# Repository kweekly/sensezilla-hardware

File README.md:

sensezilla-hardware
===================

SinBerBEST Sensing Project [hardware projects]

Contains EAGLE files for the circuit boards we are building for power_monitoring, radio boards, etc..

Do not commit EAGLE's massive ammount of "undo" files (should be handled by .gitignore)

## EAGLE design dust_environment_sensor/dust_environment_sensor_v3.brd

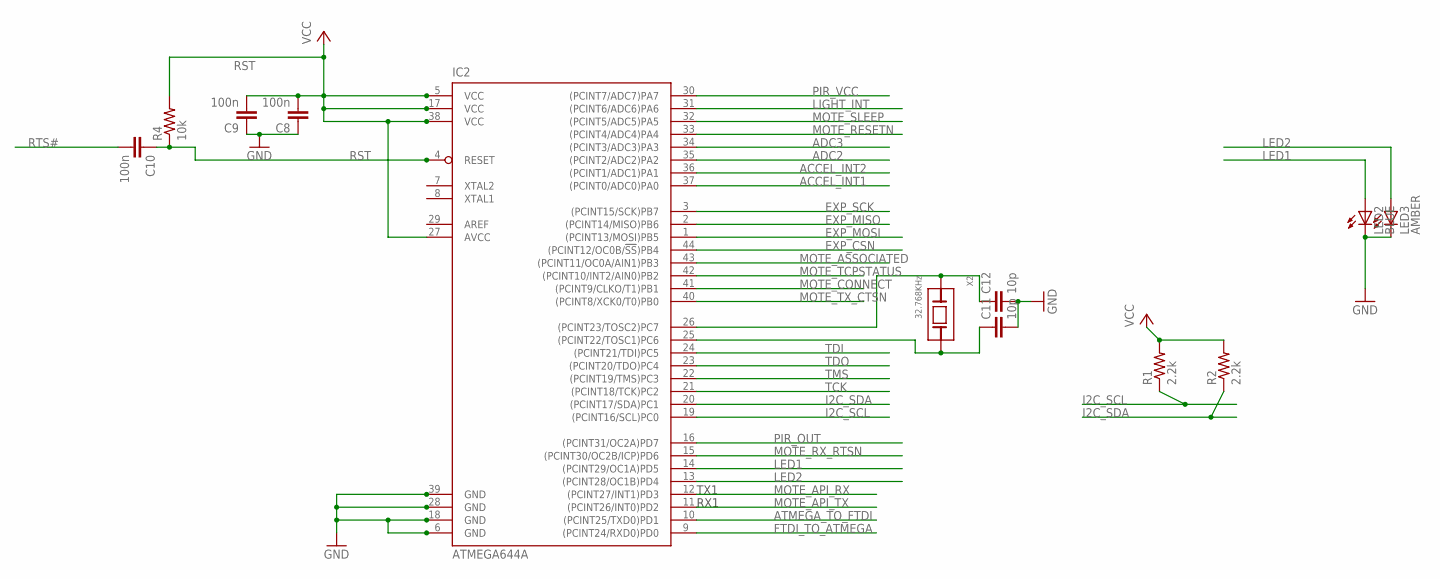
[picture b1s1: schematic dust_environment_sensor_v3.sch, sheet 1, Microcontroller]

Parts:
C8, C9, C10: 100n; C0603
C11, C12: 10p; C0603
IC2: ATMEGA644A; TQFP44
LED2: BLUE; CHIPLED_0805
LED3: AMBER; CHIPLED_0805
R1, R2: 2.2k; R0603
R4: 10k; R0603
X2: 32.768KHz; ABS07

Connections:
ACCEL_INT1: IC2.37 ((PCINT0/ADC0)PA0); also elsewhere on the board
ACCEL_INT2: IC2.36 ((PCINT1/ADC1)PA1); also elsewhere on the board
ADC2: IC2.35 ((PCINT2/ADC2)PA2); also elsewhere on the board
ADC3: IC2.34 ((PCINT3/ADC3)PA3); also elsewhere on the board
ATMEGA_TO_FTDI: IC2.10 ((PCINT25/TXD0)PD1); also elsewhere on the board
EXP_CSN: IC2.44 ((PCINT12/OC0B/!SS!)PB4); also elsewhere on the board
EXP_MISO: IC2.2 ((PCINT14/MISO)PB6); also elsewhere on the board
EXP_MOSI: IC2.1 ((PCINT13/MOSI)PB5); also elsewhere on the board
EXP_SCK: IC2.3 ((PCINT15/SCK)PB7); also elsewhere on the board
FTDI_TO_ATMEGA: IC2.9 ((PCINT24/RXD0)PD0); also elsewhere on the board
GND: C8.1, C9.1, C11.2, C12.2, IC2.6 (GND), IC2.18 (GND), IC2.28 (GND), IC2.39 (GND), LED2.C, LED3.C; also elsewhere on the board
I2C_SCL: IC2.19 ((PCINT16/SCL)PC0), R1.1; also elsewhere on the board
I2C_SDA: IC2.20 ((PCINT17/SDA)PC1), R2.1; also elsewhere on the board
LED1: IC2.14 ((PCINT29/OC1A)PD5), LED2.A
LED2: IC2.13 ((PCINT28/OC1B)PD4), LED3.A
LIGHT_INT: IC2.31 ((PCINT6/ADC6)PA6); also elsewhere on the board
MOTE_API_RX: IC2.12 ((PCINT27/INT1)PD3); also elsewhere on the board
MOTE_API_TX: IC2.11 ((PCINT26/INT0)PD2); also elsewhere on the board
MOTE_ASSOCIATED: IC2.43 ((PCINT11/OC0A/AIN1)PB3); also elsewhere on the board
MOTE_CONNECT: IC2.41 ((PCINT9/CLKO/T1)PB1); also elsewhere on the board
MOTE_RESETN: IC2.33 ((PCINT4/ADC4)PA4); also elsewhere on the board
MOTE_RX_RTSN: IC2.15 ((PCINT30/OC2B/ICP)PD6); also elsewhere on the board
MOTE_SLEEP: IC2.32 ((PCINT5/ADC5)PA5); also elsewhere on the board
MOTE_TCPSTATUS: IC2.42 ((PCINT10/INT2/AIN0)PB2); also elsewhere on the board
MOTE_TX_CTSN: IC2.40 ((PCINT8/XCK0/T0)PB0); also elsewhere on the board
unnamed: C11.1, IC2.25 ((PCINT22/TOSC1)PC6), X2.2 (B)
unnamed: C12.1, IC2.26 ((PCINT23/TOSC2)PC7), X2.1 (A)
PIR_OUT: IC2.16 ((PCINT31/OC2A)PD7); also elsewhere on the board
PIR_VCC: IC2.30 ((PCINT7/ADC7)PA7); also elsewhere on the board
RST: C10.1, IC2.4 (RESET), R4.1; also elsewhere on the board
RTS#: C10.2; also elsewhere on the board
TCK: IC2.21 ((PCINT18/TCK)PC2); also elsewhere on the board
TDI: IC2.24 ((PCINT21/TDI)PC5); also elsewhere on the board
TDO: IC2.23 ((PCINT20/TDO)PC4); also elsewhere on the board
TMS: IC2.22 ((PCINT19/TMS)PC3); also elsewhere on the board
VCC: C8.2, C9.2, IC2.5 (VCC), IC2.17 (VCC), IC2.27 (AVCC), IC2.38 (VCC), R1.2, R2.2, R4.2; also elsewhere on the board

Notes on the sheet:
TX1
RX1

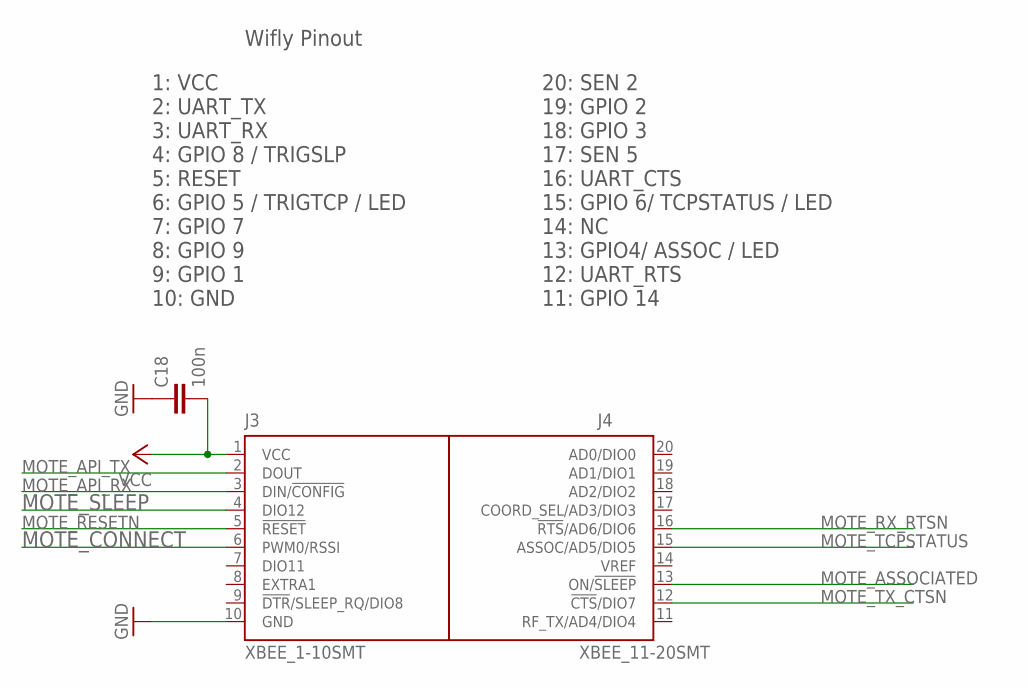
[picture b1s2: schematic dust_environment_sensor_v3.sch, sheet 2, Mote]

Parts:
C18: 100n; C0603
J3: XBEE_1-10SMT; XBEE_1-10_SMT
J4: XBEE_11-20SMT; XBEE_11-20_SMT

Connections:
GND: C18.1, J3.10 (GND); also elsewhere on the board
MOTE_API_RX: J3.3 (DIN/!CONFIG); also elsewhere on the board
MOTE_API_TX: J3.2 (DOUT); also elsewhere on the board
MOTE_ASSOCIATED: J4.13 (ON/!SLEEP); also elsewhere on the board
MOTE_CONNECT: J3.6 (PWM0/RSSI); also elsewhere on the board
MOTE_RESETN: J3.5 (!RESET); also elsewhere on the board
MOTE_RX_RTSN: J4.16 (!RTS!/AD6/DIO6); also elsewhere on the board
MOTE_SLEEP: J3.4 (DIO12); also elsewhere on the board
MOTE_TCPSTATUS: J4.15 (ASSOC/AD5/DIO5); also elsewhere on the board
MOTE_TX_CTSN: J4.12 (!CTS!/DIO7); also elsewhere on the board
VCC: C18.2, J3.1 (VCC); also elsewhere on the board

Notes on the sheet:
Wifly Pinout
1: VCC 2: UART_TX 3: UART_RX 4: GPIO 8 / TRIGSLP 5: RESET 6: GPIO 5 / TRIGTCP / LED 7: GPIO 7 8: GPIO 9 9: GPIO 1 10: GND
20: SEN 2 19: GPIO 2 18: GPIO 3 17: SEN 5 16: UART_CTS 15: GPIO 6/ TCPSTATUS / LED 14: NC 13: GPIO4/ ASSOC / LED 12: UART_RTS 11: GPIO 14

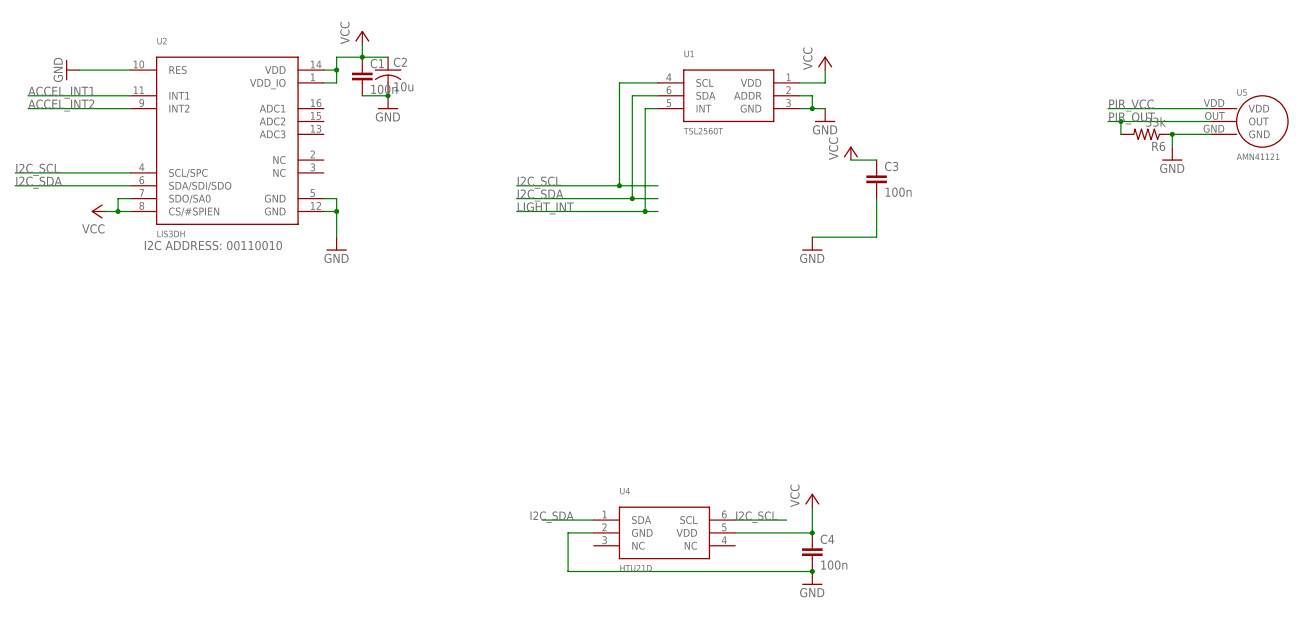
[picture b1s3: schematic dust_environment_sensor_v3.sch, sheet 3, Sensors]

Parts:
C1, C3, C4: 100n; C0603
C2: 10u; C0603
R6: 33k; R0603
U1: TSL2560T; T_TAOS
U2: LIS3DH; LGA16_ST
U4: HTU21D
U5: AMN41121

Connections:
ACCEL_INT1: U2.11 (INT1); also elsewhere on the board
ACCEL_INT2: U2.9 (INT2); also elsewhere on the board
GND: C1.2, C2.2, C3.2, C4.2, R6.1, U1.2 (ADDR), U1.3 (GND), U2.5 (GND), U2.10 (RES), U2.12 (GND), U4.2 (GND), U5.GND; also elsewhere on the board
I2C_SCL: U1.4 (SCL), U2.4 (SCL/SPC), U4.6 (SCL); also elsewhere on the board
I2C_SDA: U1.6 (SDA), U2.6 (SDA/SDI/SDO), U4.1 (SDA); also elsewhere on the board
LIGHT_INT: U1.5 (INT); also elsewhere on the board
PIR_OUT: R6.2, U5.OUT; also elsewhere on the board
PIR_VCC: U5.VDD; also elsewhere on the board
VCC: C1.1, C2.1, C3.1, C4.1, U1.1 (VDD), U2.1 (VDD_IO), U2.7 (SDO/SA0), U2.8 (CS/#SPIEN), U2.14 (VDD), U4.5 (VDD); also elsewhere on the board

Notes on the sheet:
I2C ADDRESS: 00110010

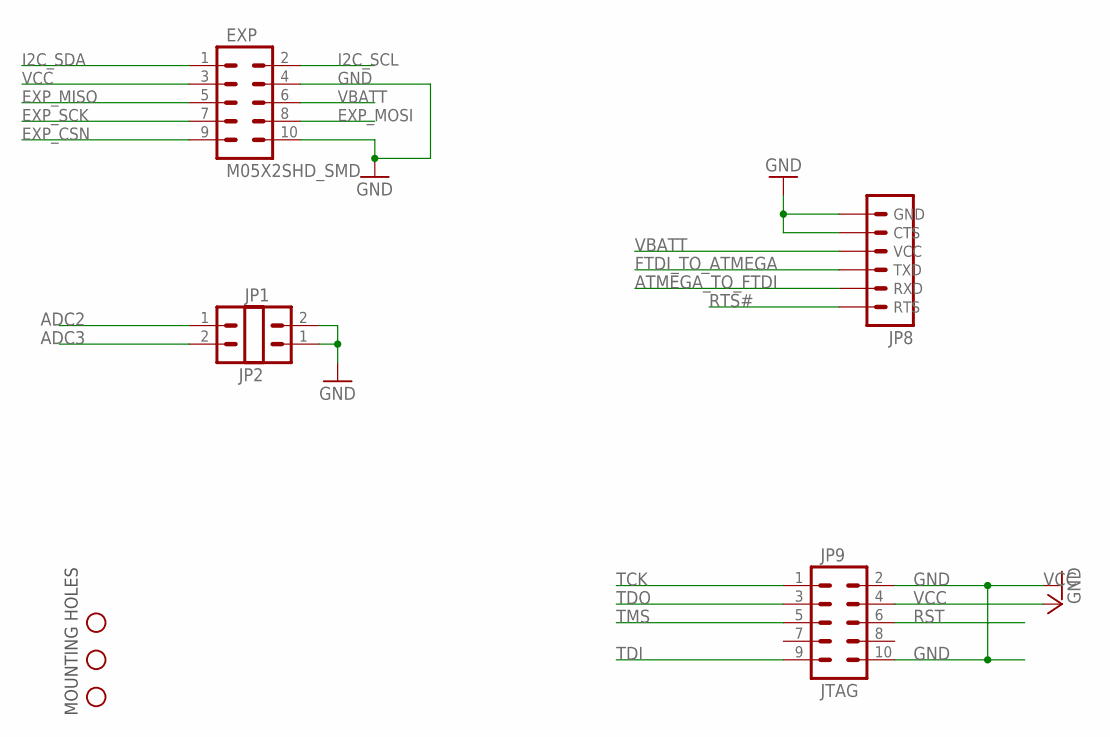
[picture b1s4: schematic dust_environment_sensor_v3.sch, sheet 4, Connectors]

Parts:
EXP: M05X2SHD_SMD; 2X5-SHROUDED_SMD
JP1, JP2: M02PTH; 1X02
JP8: FTDI_CABLESIP; 1X06
JP9: JTAG; 2X5-SHROUDED_SMD
STANDOFF1, STANDOFF2, STANDOFF3: STAND-OFF

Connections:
ADC2: JP2.1; also elsewhere on the board
ADC3: JP2.2; also elsewhere on the board
ATMEGA_TO_FTDI: JP8.5 (RXD); also elsewhere on the board
EXP_CSN: EXP.9; also elsewhere on the board
EXP_MISO: EXP.5; also elsewhere on the board
EXP_MOSI: EXP.8; also elsewhere on the board
EXP_SCK: EXP.7; also elsewhere on the board
FTDI_TO_ATMEGA: JP8.4 (TXD); also elsewhere on the board
GND: EXP.4, EXP.10, JP1.1, JP1.2, JP8.1 (GND), JP8.2 (CTS), JP9.2, JP9.10; also elsewhere on the board
I2C_SCL: EXP.2; also elsewhere on the board
I2C_SDA: EXP.1; also elsewhere on the board
RST: JP9.6; also elsewhere on the board
RTS#: JP8.6 (RTS); also elsewhere on the board
TCK: JP9.1; also elsewhere on the board
TDI: JP9.9; also elsewhere on the board
TDO: JP9.3; also elsewhere on the board
TMS: JP9.5; also elsewhere on the board
VBATT: EXP.6, JP8.3 (VCC); also elsewhere on the board
VCC: EXP.3, JP9.4; also elsewhere on the board

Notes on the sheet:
MOUNTING HOLES

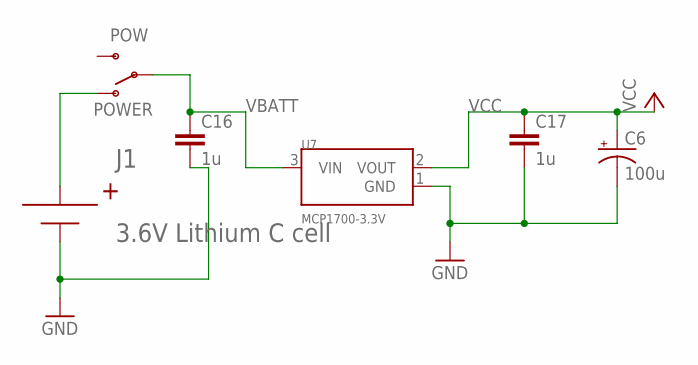
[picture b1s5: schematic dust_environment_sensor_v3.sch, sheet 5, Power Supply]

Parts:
C6: 100u; EIA7343
C16, C17: 1u; C0603
J1: 3.6V Lithium C cell; BX0036_NOHOLES
POW: POWER; JS102011SAQN
U7: MCP1700-3.3V; SOT23-3

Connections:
GND: C6.C (-), C16.2, C17.2, J1.NEG, U7.1 (GND); also elsewhere on the board
unnamed: J1.POS, POW.1 (O)
VBATT: C16.1, POW.C, U7.3 (VIN); also elsewhere on the board
VCC: C6.A (+), C17.1, U7.2 (VOUT); also elsewhere on the board

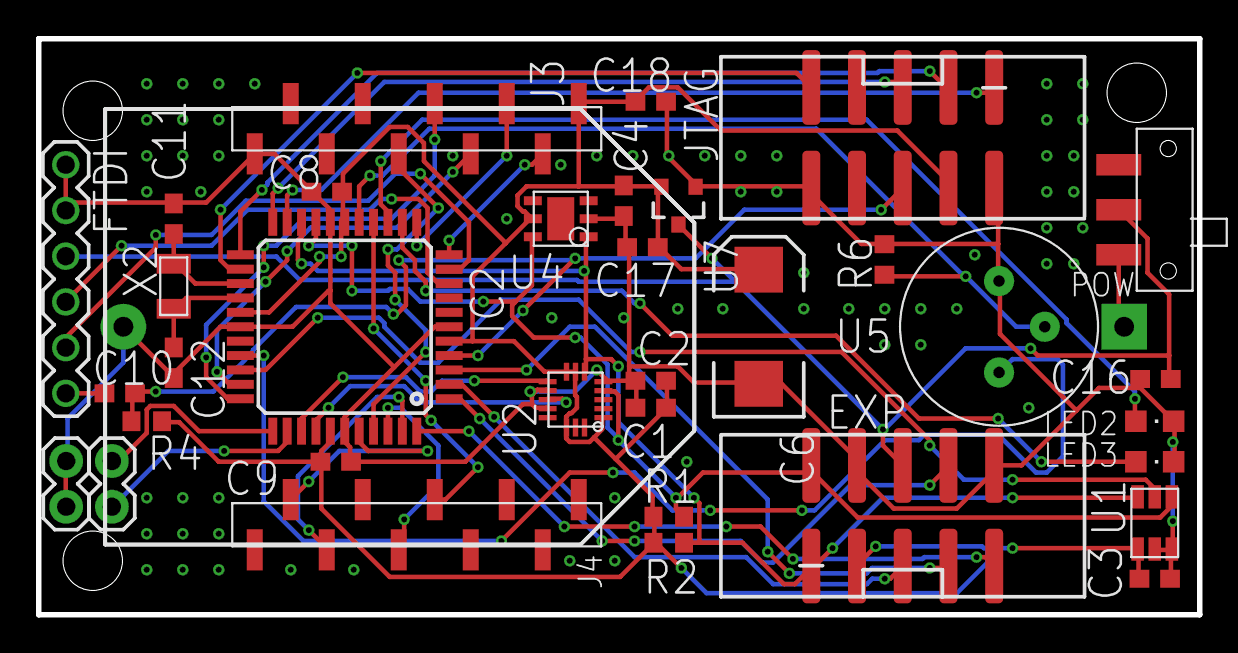
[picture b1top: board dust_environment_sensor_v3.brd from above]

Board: 2 copper layers, 64.5 x 32.0 mm, 38 parts (1 on the bottom side), 38 nets.

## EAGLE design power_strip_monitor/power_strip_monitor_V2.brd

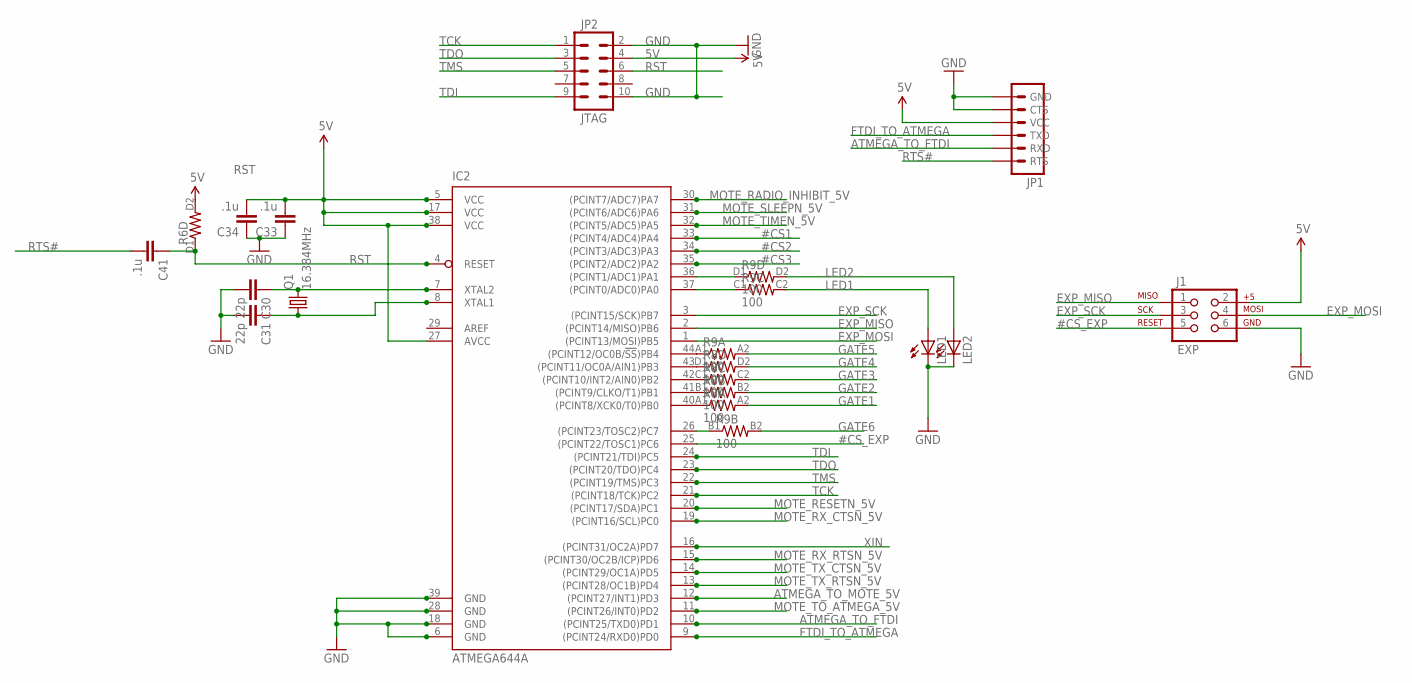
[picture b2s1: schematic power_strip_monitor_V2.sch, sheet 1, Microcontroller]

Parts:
C30, C31: 22p; 0603
C33, C34, C41: .1u; 0603
IC2: ATMEGA644A; TQFP44
J1: EXP; 2X3
JP1: FTDI_CABLESIP; 1X06
JP2: JTAG; AVR_ICSP
LED1, LED2: LEDCHIPLED_0805; CHIPLED_0805
Q1: 16.384MHz; HC49UP
R6: RESISTOR-ARRAY; 1206_NETWORK
R8, R9: 100; 1206_NETWORK

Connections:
5V: C33.2, C34.2, IC2.5 (VCC), IC2.17 (VCC), IC2.27 (AVCC), IC2.38 (VCC), J1.2, JP1.3 (VCC), JP2.4, R6.D2 (2); also elsewhere on the board
#CS1: IC2.33 ((PCINT4/ADC4)PA4); also elsewhere on the board
#CS2: IC2.34 ((PCINT3/ADC3)PA3); also elsewhere on the board
#CS3: IC2.35 ((PCINT2/ADC2)PA2); also elsewhere on the board
#CS_EXP: IC2.25 ((PCINT22/TOSC1)PC6), J1.5
ATMEGA_TO_FTDI: IC2.10 ((PCINT25/TXD0)PD1), JP1.5 (RXD)
ATMEGA_TO_MOTE_5V: IC2.12 ((PCINT27/INT1)PD3); also elsewhere on the board
EXP_MISO: IC2.2 ((PCINT14/MISO)PB6), J1.1
EXP_MOSI: IC2.1 ((PCINT13/MOSI)PB5), J1.4
EXP_SCK: IC2.3 ((PCINT15/SCK)PB7), J1.3
FTDI_TO_ATMEGA: IC2.9 ((PCINT24/RXD0)PD0), JP1.4 (TXD)
GATE1: R8.A2 (2); also elsewhere on the board
GATE2: R8.B2 (2); also elsewhere on the board
GATE3: R8.C2 (2); also elsewhere on the board
GATE4: R8.D2 (2); also elsewhere on the board
GATE5: R9.A2 (2); also elsewhere on the board
GATE6: R9.B2 (2); also elsewhere on the board
GND: C30.2, C31.2, C33.1, C34.1, IC2.6 (GND), IC2.18 (GND), IC2.28 (GND), IC2.39 (GND), J1.6, JP1.1 (GND), JP1.2 (CTS), JP2.2, JP2.10, LED1.C, LED2.C; also elsewhere on the board
LED1: LED1.A, R9.C2 (2)
LED2: LED2.A, R9.D2 (2)
MOTE_RADIO_INHIBIT_5V: IC2.30 ((PCINT7/ADC7)PA7); also elsewhere on the board
MOTE_RESETN_5V: IC2.20 ((PCINT17/SDA)PC1); also elsewhere on the board
MOTE_RX_CTSN_5V: IC2.19 ((PCINT16/SCL)PC0); also elsewhere on the board
MOTE_RX_RTSN_5V: IC2.15 ((PCINT30/OC2B/ICP)PD6); also elsewhere on the board
MOTE_SLEEPN_5V: IC2.31 ((PCINT6/ADC6)PA6); also elsewhere on the board
MOTE_TIMEN_5V: IC2.32 ((PCINT5/ADC5)PA5); also elsewhere on the board
MOTE_TO_ATMEGA_5V: IC2.11 ((PCINT26/INT0)PD2); also elsewhere on the board
MOTE_TX_CTSN_5V: IC2.14 ((PCINT29/OC1A)PD5); also elsewhere on the board
MOTE_TX_RTSN_5V: IC2.13 ((PCINT28/OC1B)PD4); also elsewhere on the board
unnamed: C30.1, IC2.7 (XTAL2), Q1.2
unnamed: C31.1, IC2.8 (XTAL1), Q1.1
unnamed: IC2.40 ((PCINT8/XCK0/T0)PB0), R8.A1 (1)
unnamed: IC2.41 ((PCINT9/CLKO/T1)PB1), R8.B1 (1)
unnamed: IC2.42 ((PCINT10/INT2/AIN0)PB2), R8.C1 (1)
unnamed: IC2.43 ((PCINT11/OC0A/AIN1)PB3), R8.D1 (1)
unnamed: IC2.44 ((PCINT12/OC0B/!SS!)PB4), R9.A1 (1)
unnamed: IC2.26 ((PCINT23/TOSC2)PC7), R9.B1 (1)
unnamed: IC2.36 ((PCINT1/ADC1)PA1), R9.D1 (1)
unnamed: IC2.37 ((PCINT0/ADC0)PA0), R9.C1 (1)
RST: C41.1, IC2.4 (RESET), JP2.6, R6.D1 (1)
RTS#: C41.2, JP1.6 (RTS)
TCK: IC2.21 ((PCINT18/TCK)PC2), JP2.1
TDI: IC2.24 ((PCINT21/TDI)PC5), JP2.9
TDO: IC2.23 ((PCINT20/TDO)PC4), JP2.3
TMS: IC2.22 ((PCINT19/TMS)PC3), JP2.5
XIN: IC2.16 ((PCINT31/OC2A)PD7); also elsewhere on the board

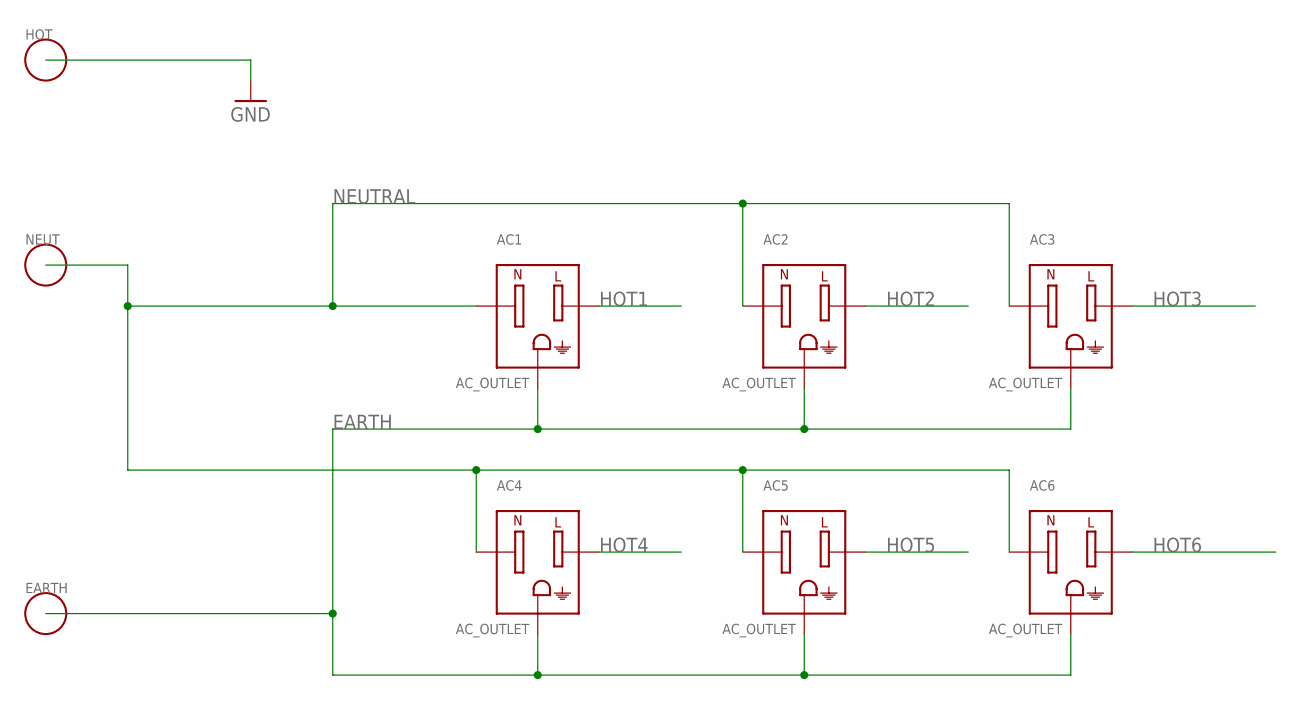
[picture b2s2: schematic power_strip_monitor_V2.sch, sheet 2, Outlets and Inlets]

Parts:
AC1, AC2, AC3, AC4, AC5, AC6: AC_OUTLET; 3-213598-2
EARTH: 1P_HOLE; 14GAUGE_HOLE
HOT: 1P_HOLE; 14GAUGE_HOLE
NEUT: 1P_HOLE; 14GAUGE_HOLE

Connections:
EARTH: AC1.3 (EARTH), AC2.3 (EARTH), AC3.3 (EARTH), AC4.3 (EARTH), AC5.3 (EARTH), AC6.3 (EARTH), EARTH.P$1
GND: HOT.P$1; also elsewhere on the board
HOT1: AC1.2 (L); also elsewhere on the board
HOT2: AC2.2 (L); also elsewhere on the board
HOT3: AC3.2 (L); also elsewhere on the board
HOT4: AC4.2 (L); also elsewhere on the board
HOT5: AC5.2 (L); also elsewhere on the board
HOT6: AC6.2 (L); also elsewhere on the board
NEUTRAL: AC1.1 (N), AC2.1 (N), AC3.1 (N), AC4.1 (N), AC5.1 (N), AC6.1 (N), NEUT.P$1; also elsewhere on the board

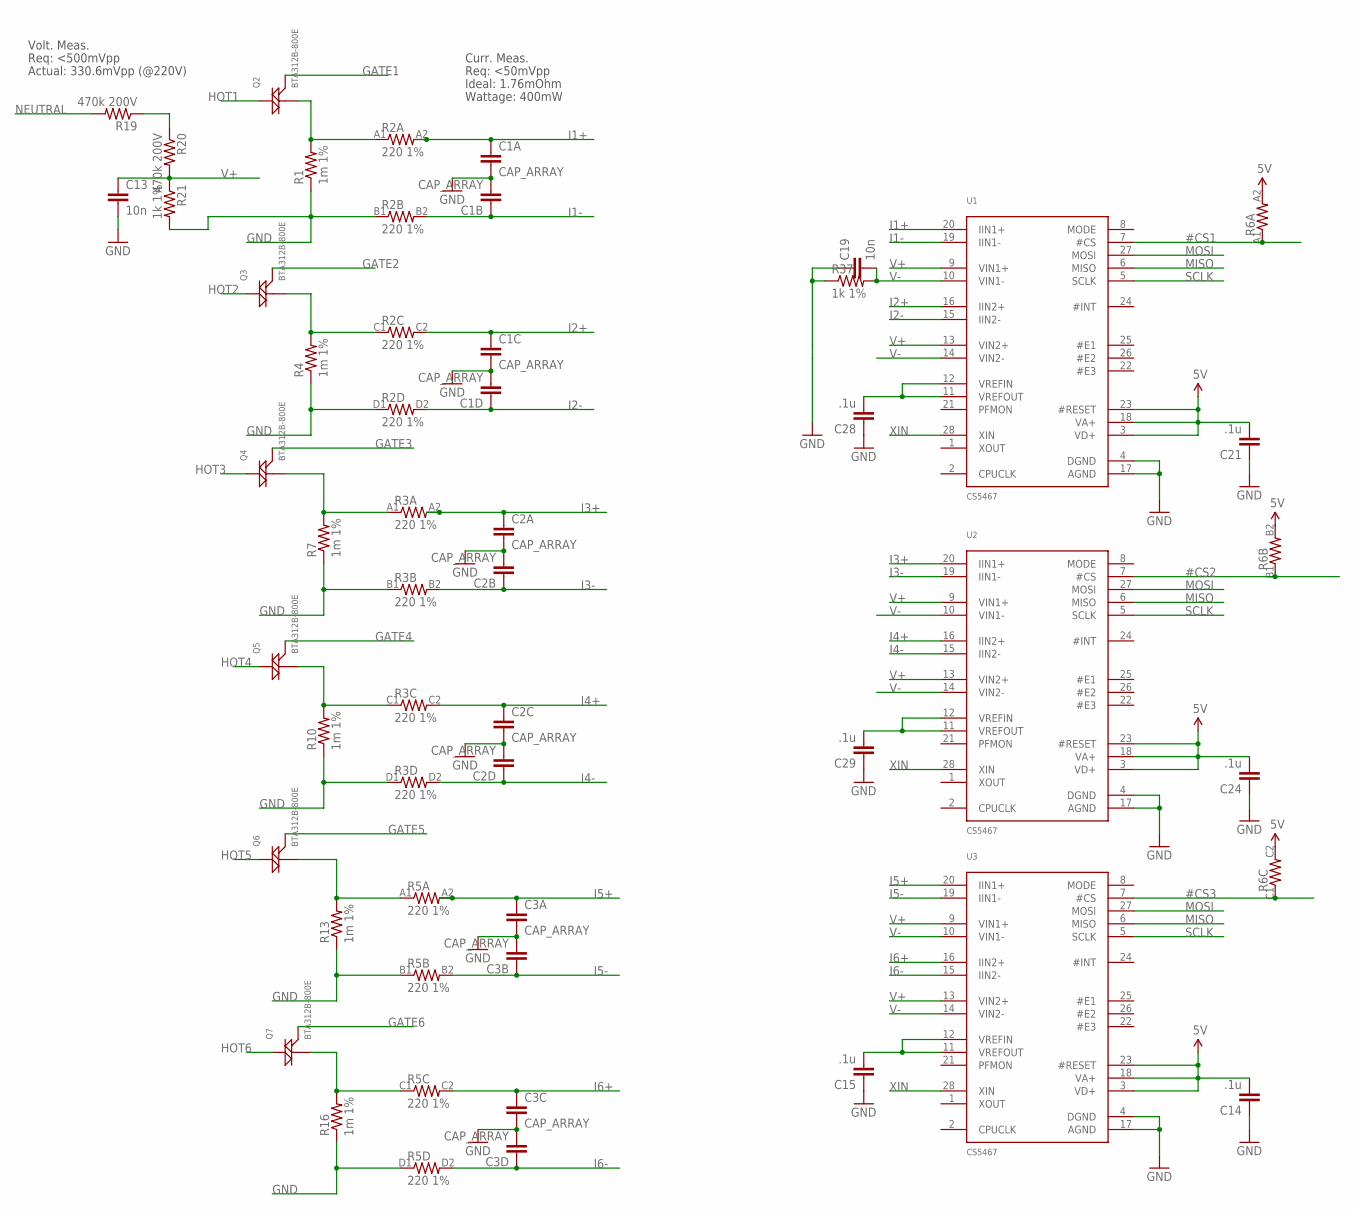
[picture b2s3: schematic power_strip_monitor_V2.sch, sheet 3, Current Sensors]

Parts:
C1, C2, C3: CAP_ARRAY; 1206_NETWORK
C13, C19: 10n; 0603
C14, C15, C21, C24, C28, C29: .1u; 0603
Q2, Q3, Q4, Q5, Q6, Q7: BTA312B-800E; D2PACK_NXP
R1, R4, R7, R10, R13, R16: 1m 1%; R2512
R2, R3, R5: 220 1%; 1206_NETWORK
R6: RESISTOR-ARRAY; 1206_NETWORK
R19, R20: 470k 200V; 1206
R21, R37: 1k 1%; 0603
U1, U2, U3: CS5467; SSOP28L_CIRRUS

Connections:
5V: C14.2, C21.2, C24.2, R6.A2 (2), R6.B2 (2), R6.C2 (2), U1.3 (VD+), U1.18 (VA+), U1.23 (#RESET), U2.3 (VD+), U2.18 (VA+), U2.23 (#RESET), U3.3 (VD+), U3.18 (VA+), U3.23 (#RESET); also elsewhere on the board
#CS1: R6.A1 (1), U1.7 (#CS); also elsewhere on the board
#CS2: R6.B1 (1), U2.7 (#CS); also elsewhere on the board
#CS3: R6.C1 (1), U3.7 (#CS); also elsewhere on the board
GATE1: Q2.3 (G); also elsewhere on the board
GATE2: Q3.3 (G); also elsewhere on the board
GATE3: Q4.3 (G); also elsewhere on the board
GATE4: Q5.3 (G); also elsewhere on the board
GATE5: Q6.3 (G); also elsewhere on the board
GATE6: Q7.3 (G); also elsewhere on the board
GND: C1.A2 (2), C1.B2 (2), C1.C2 (2), C1.D2 (2), C2.A2 (2), C2.B2 (2), C2.C2 (2), C2.D2 (2), C3.A2 (2), C3.B2 (2), C3.C2 (2), C3.D2 (2), C13.2, C14.1, C15.1, C19.1, C21.1, C24.1, C28.1, C29.1, R1.1, R2.B1 (1), R2.D1 (1), R3.B1 (1), R3.D1 (1), R4.1, R5.B1 (1), R5.D1 (1), R7.1, R10.1, R13.1, R16.1, R21.2, R37.1, U1.4 (DGND), U1.17 (AGND), U2.4 (DGND), U2.17 (AGND), U3.4 (DGND), U3.17 (AGND); also elsewhere on the board
HOT1: Q2.2 (M2); also elsewhere on the board
HOT2: Q3.2 (M2); also elsewhere on the board
HOT3: Q4.2 (M2); also elsewhere on the board
HOT4: Q5.2 (M2); also elsewhere on the board
HOT5: Q6.2 (M2); also elsewhere on the board
HOT6: Q7.2 (M2); also elsewhere on the board
HRET1: Q2.1 (M1), R1.2, R2.A1 (1)
HRET2: Q3.1 (M1), R2.C1 (1), R4.2
HRET3: Q4.1 (M1), R3.A1 (1), R7.2
HRET4: Q5.1 (M1), R3.C1 (1), R10.2
HRET5: Q6.1 (M1), R5.A1 (1), R13.2
HRET6: Q7.1 (M1), R5.C1 (1), R16.2
I1+: C1.A1 (1), R2.A2 (2), U1.20 (IIN1+)
I1-: C1.B1 (1), R2.B2 (2), U1.19 (IIN1-)
I2+: C1.C1 (1), R2.C2 (2), U1.16 (IIN2+)
I2-: C1.D1 (1), R2.D2 (2), U1.15 (IIN2-)
I3+: C2.A1 (1), R3.A2 (2), U2.20 (IIN1+)
I3-: C2.B1 (1), R3.B2 (2), U2.19 (IIN1-)
I4+: C2.C1 (1), R3.C2 (2), U2.16 (IIN2+)
I4-: C2.D1 (1), R3.D2 (2), U2.15 (IIN2-)
I5+: C3.A1 (1), R5.A2 (2), U3.20 (IIN1+)
I5-: C3.B1 (1), R5.B2 (2), U3.19 (IIN1-)
I6+: C3.C1 (1), R5.C2 (2), U3.16 (IIN2+)
I6-: C3.D1 (1), R5.D2 (2), U3.15 (IIN2-)
MISO: U1.6 (MISO), U2.6 (MISO), U3.6 (MISO)
MOSI: U1.27 (MOSI), U2.27 (MOSI), U3.27 (MOSI)
unnamed: R19.1, R20.1
unnamed: C15.2, U3.11 (VREFOUT), U3.12 (VREFIN)
unnamed: C29.2, U2.11 (VREFOUT), U2.12 (VREFIN)
unnamed: C28.2, U1.11 (VREFOUT), U1.12 (VREFIN)
NEUTRAL: R19.2; also elsewhere on the board
SCLK: U1.5 (SCLK), U2.5 (SCLK), U3.5 (SCLK)
V+: C13.1, R20.2, R21.1, U1.9 (VIN1+), U1.13 (VIN2+), U2.9 (VIN1+), U2.13 (VIN2+), U3.9 (VIN1+), U3.13 (VIN2+)
V-: C19.2, R37.2, U1.10 (VIN1-), U1.14 (VIN2-), U2.10 (VIN1-), U2.14 (VIN2-), U3.10 (VIN1-), U3.14 (VIN2-)
XIN: U1.28 (XIN), U2.28 (XIN), U3.28 (XIN); also elsewhere on the board

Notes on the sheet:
Req: <500mVpp
Actual: 330.6mVpp (@220V)
Volt. Meas.
Curr. Meas.
Req: <50mVpp
Ideal: 1.76mOhm
Wattage: 400mW

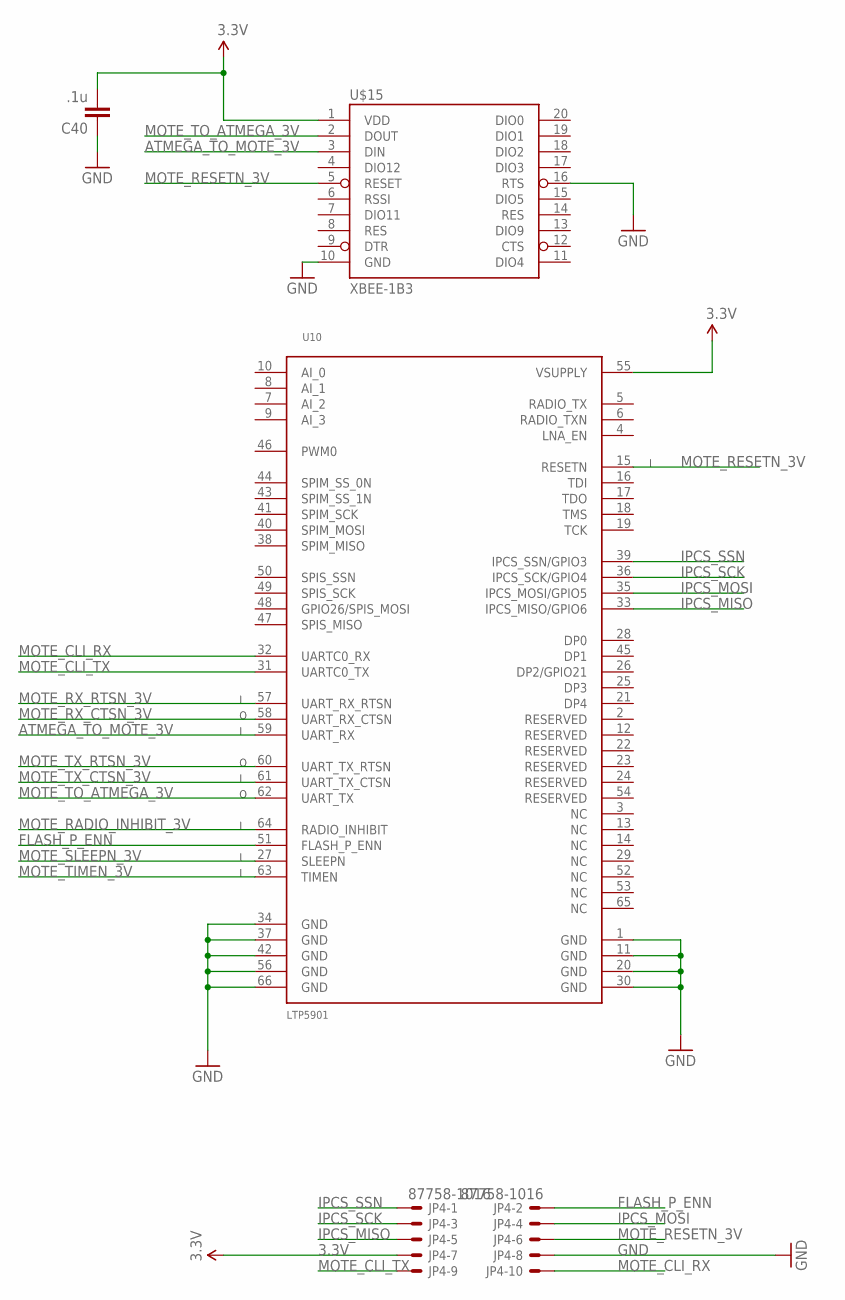
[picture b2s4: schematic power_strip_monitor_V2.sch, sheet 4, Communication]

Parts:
C40: .1u; 0603
JP4: 87758-1016
U10: LTP5901; LTP5901_MODULE
U$15: XBEE-1B3; XBEE-SMD

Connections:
3.3V: C40.2, JP4.7, U10.55 (VSUPPLY), U$15.1 (VDD); also elsewhere on the board
ATMEGA_TO_MOTE_3V: U10.59 (UART_RX), U$15.3 (DIN); also elsewhere on the board
FLASH_P_ENN: JP4.2, U10.51 (FLASH_P_ENN)
GND: C40.1, JP4.8, U10.1 (GND), U10.11 (GND), U10.20 (GND), U10.30 (GND), U10.34 (GND), U10.37 (GND), U10.42 (GND), U10.56 (GND), U10.66 (GND), U$15.10 (GND), U$15.16 (RTS); also elsewhere on the board
IPCS_MISO: JP4.5, U10.33 (IPCS_MISO/GPIO6)
IPCS_MOSI: JP4.4, U10.35 (IPCS_MOSI/GPIO5)
IPCS_SCK: JP4.3, U10.36 (IPCS_SCK/GPIO4)
IPCS_SSN: JP4.1, U10.39 (IPCS_SSN/GPIO3)
MOTE_CLI_RX: JP4.10, U10.32 (UARTC0_RX)
MOTE_CLI_TX: JP4.9, U10.31 (UARTC0_TX)
MOTE_RADIO_INHIBIT_3V: U10.64 (RADIO_INHIBIT); also elsewhere on the board
MOTE_RESETN_3V: JP4.6, U10.15 (RESETN), U$15.5 (RESET); also elsewhere on the board
MOTE_RX_CTSN_3V: U10.58 (UART_RX_CTSN); also elsewhere on the board
MOTE_RX_RTSN_3V: U10.57 (UART_RX_RTSN); also elsewhere on the board
MOTE_SLEEPN_3V: U10.27 (SLEEPN); also elsewhere on the board
MOTE_TIMEN_3V: U10.63 (TIMEN); also elsewhere on the board
MOTE_TO_ATMEGA_3V: U10.62 (UART_TX), U$15.2 (DOUT); also elsewhere on the board
MOTE_TX_CTSN_3V: U10.61 (UART_TX_CTSN); also elsewhere on the board
MOTE_TX_RTSN_3V: U10.60 (UART_TX_RTSN); also elsewhere on the board

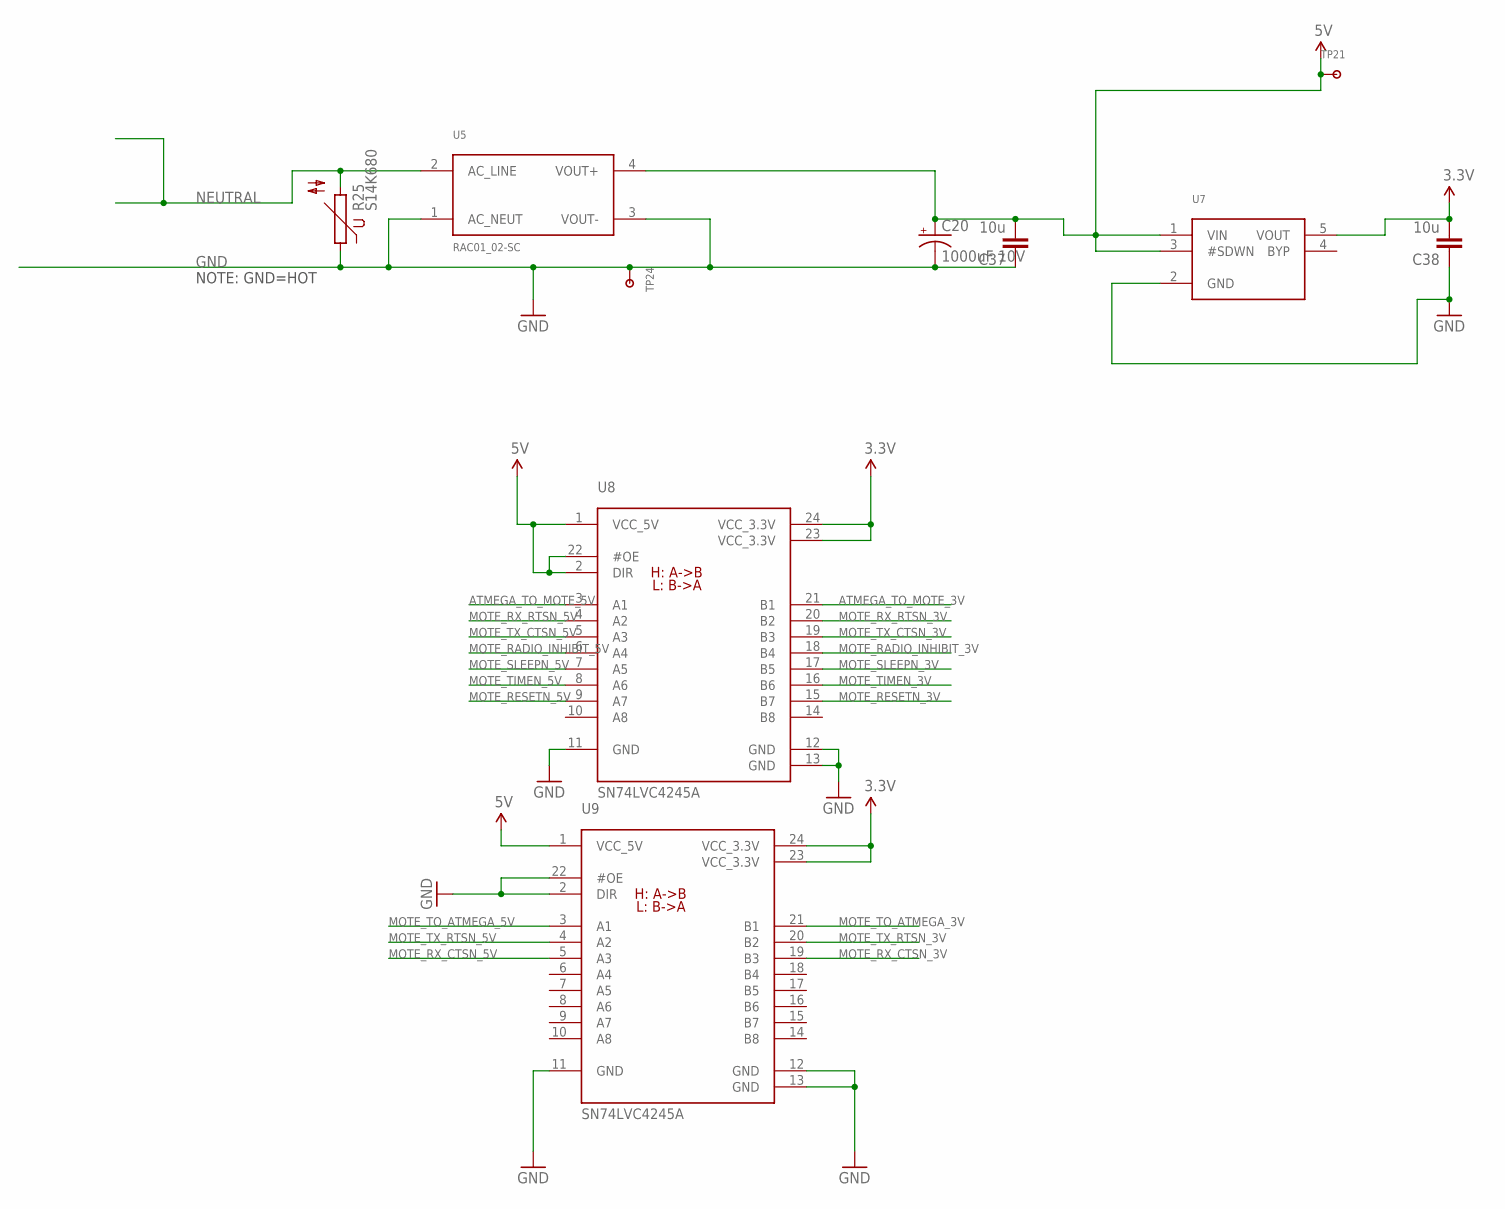
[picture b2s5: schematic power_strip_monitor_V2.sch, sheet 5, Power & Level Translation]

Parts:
C20: 1000uF 10V; CPOL-RADIAL-1000UF-63V
C37, C38: 10u; 0603
R25: S14K680
TP21, TP24: TESTPOINT100MIL; TESTPOINT-100MIL
U5: RAC01_02-SC
U7: LT1761-X; TSOT23-5_LINEAR
U8, U9: SN74LVC4245A; TSSOP24_TI

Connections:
3.3V: C38.2, U7.5 (VOUT), U8.23 (VCC_3.3V), U8.24 (VCC_3.3V), U9.23 (VCC_3.3V), U9.24 (VCC_3.3V); also elsewhere on the board
5V: C20.1 (+), C37.2, TP21.2, U5.4 (VOUT+), U7.1 (VIN), U7.3 (#SDWN), U8.1 (VCC_5V), U8.2 (DIR), U8.22 (#OE), U9.1 (VCC_5V); also elsewhere on the board
ATMEGA_TO_MOTE_3V: U8.21 (B1); also elsewhere on the board
ATMEGA_TO_MOTE_5V: U8.3 (A1); also elsewhere on the board
GND: C20.2 (-), C37.1, C38.1, R25.1, TP24.2, U5.1 (AC_NEUT), U5.3 (VOUT-), U7.2 (GND), U8.11 (GND), U8.12 (GND), U8.13 (GND), U9.2 (DIR), U9.11 (GND), U9.12 (GND), U9.13 (GND), U9.22 (#OE); also elsewhere on the board
MOTE_RADIO_INHIBIT_3V: U8.18 (B4); also elsewhere on the board
MOTE_RADIO_INHIBIT_5V: U8.6 (A4); also elsewhere on the board
MOTE_RESETN_3V: U8.15 (B7); also elsewhere on the board
MOTE_RESETN_5V: U8.9 (A7); also elsewhere on the board
MOTE_RX_CTSN_3V: U9.19 (B3); also elsewhere on the board
MOTE_RX_CTSN_5V: U9.5 (A3); also elsewhere on the board
MOTE_RX_RTSN_3V: U8.20 (B2); also elsewhere on the board
MOTE_RX_RTSN_5V: U8.4 (A2); also elsewhere on the board
MOTE_SLEEPN_3V: U8.17 (B5); also elsewhere on the board
MOTE_SLEEPN_5V: U8.7 (A5); also elsewhere on the board
MOTE_TIMEN_3V: U8.16 (B6); also elsewhere on the board
MOTE_TIMEN_5V: U8.8 (A6); also elsewhere on the board
MOTE_TO_ATMEGA_3V: U9.21 (B1); also elsewhere on the board
MOTE_TO_ATMEGA_5V: U9.3 (A1); also elsewhere on the board
MOTE_TX_CTSN_3V: U8.19 (B3); also elsewhere on the board
MOTE_TX_CTSN_5V: U8.5 (A3); also elsewhere on the board
MOTE_TX_RTSN_3V: U9.20 (B2); also elsewhere on the board
MOTE_TX_RTSN_5V: U9.4 (A2); also elsewhere on the board
NEUTRAL: R25.2, U5.2 (AC_LINE); also elsewhere on the board

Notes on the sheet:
NOTE: GND=HOT

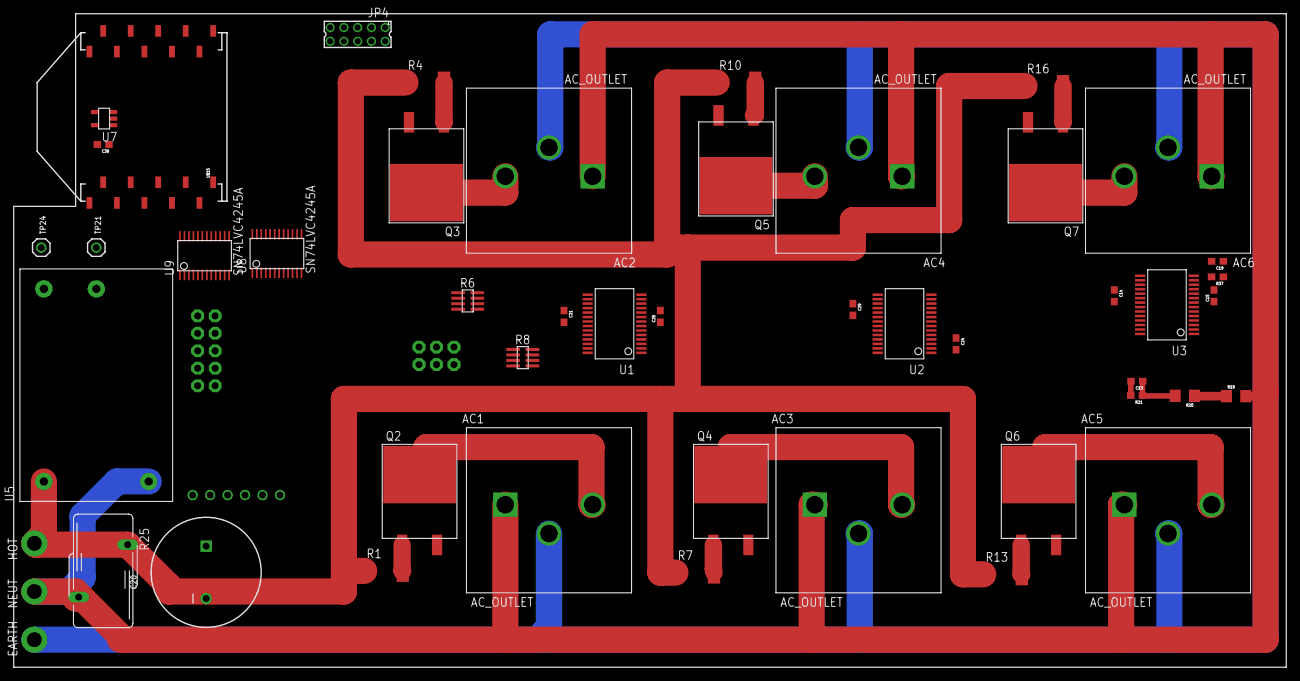
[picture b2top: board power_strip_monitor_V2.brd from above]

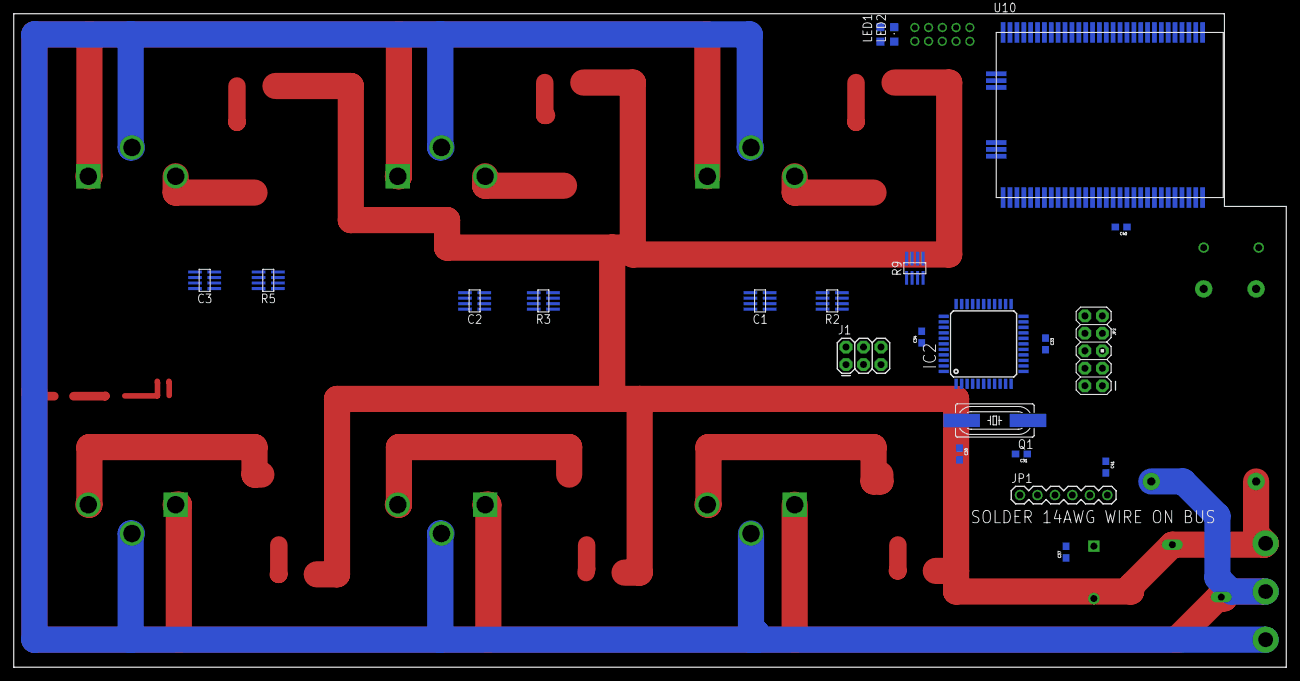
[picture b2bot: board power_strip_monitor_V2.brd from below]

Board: 4 copper layers, 185.0 x 95.0 mm, 71 parts (22 on the bottom side), 99 nets.

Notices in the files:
parts and their libraries:
SparkFun-Electromechanical: Licensing: CC v3.0 Share-Alike You are welcome to use this library for commercial purposes.
